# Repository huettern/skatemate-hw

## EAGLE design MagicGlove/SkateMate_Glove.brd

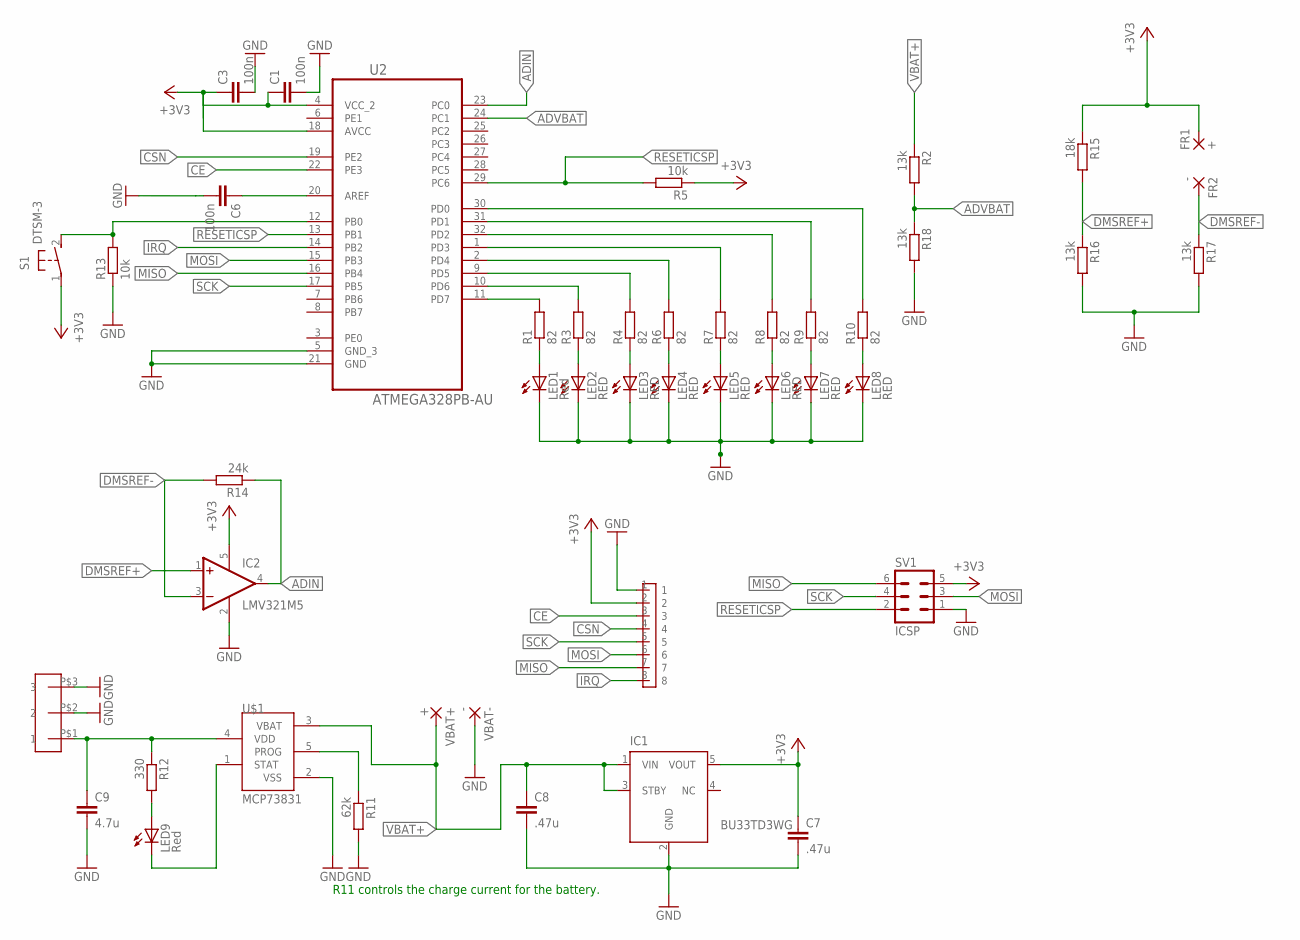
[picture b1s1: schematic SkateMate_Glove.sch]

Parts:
C1, C3, C6: 100n; C0603
C7, C8: .47u; C0603
C9: 4.7u; C0603
FR1: +; 1,6/0,8
FR2: -; 1,6/0,8
IC1: BU33TD3WG; SOT23-5
IC2: LMV321M5; SOT23-5
LED1, LED9: Red; CHIPLED_0805
LED2, LED3, LED4, LED5, LED6, LED7, LED8: RED; CHIPLED_0805
R1, R3, R4, R6, R7, R8, R9, R10: 82; R0603
R2, R16, R17, R18: 13k; R0603
R5, R13: 10k; R0603
R11: 62k; R0603
R12: 330; R0603
R14: 24k; R0603
R15: 18k; R0603
S1: DTSM-3
SV1: ICSP; MA03-2
U2: ATMEGA328PB-AU; QFP80P900X900X120-32N
U$1: MCP73831; SOT23-5L
U$2: HEADER1,27
U$3: 3PINHEADER
VBAT+: +; 1,6/0,8
VBAT-: -; 1,6/0,8

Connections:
+3V3: C1.1, C3.1, C7.1, FR1.1, IC1.5 (VOUT), IC2.5 (V+), R5.1, R15.1, S1.1, SV1.5, U2.4 (VCC_2), U2.18 (AVCC), U$2.2
ADIN: IC2.4 (OUT), R14.1, U2.23 (PC0)
ADVBAT: R2.2, R18.1, U2.24 (PC1)
CE: U2.22 (PE3), U$2.3
CSN: U2.19 (PE2), U$2.4
DMSREF+: IC2.1 (+IN), R15.2, R16.1
DMSREF-: FR2.1, IC2.3 (-IN), R14.2, R17.1
GND: C1.2, C3.2, C6.2, C7.2, C8.2, C9.2, IC1.2 (GND), IC2.2 (V-), LED1.C, LED2.C, LED3.C, LED4.C, LED5.C, LED6.C, LED7.C, LED8.C, R11.2, R13.1, R16.2, R17.2, R18.2, SV1.1, U2.5 (GND_3), U2.21 (GND), U$1.2 (VSS), U$2.1, U$3.P$2 (2), U$3.P$3 (3), VBAT-.1
IRQ: U2.14 (PB2), U$2.8
MISO: SV1.6, U2.16 (PB4), U$2.7
MOSI: SV1.3, U2.15 (PB3), U$2.6
unnamed: LED1.A, R1.1
unnamed: LED2.A, R3.1
unnamed: R13.2, S1.2, U2.12 (PB0)
unnamed: C6.1, U2.20 (AREF)
unnamed: R11.1, U$1.5 (PROG)
unnamed: LED3.A, R4.1
unnamed: LED6.A, R8.1
unnamed: LED7.A, R9.1
unnamed: LED8.A, R10.1
unnamed: LED4.A, R6.1
unnamed: LED5.A, R7.1
unnamed: R1.2, U2.11 (PD7)
unnamed: R3.2, U2.10 (PD6)
unnamed: R4.2, U2.9 (PD5)
unnamed: R6.2, U2.2 (PD4)
unnamed: R7.2, U2.1 (PD3)
unnamed: R8.2, U2.32 (PD2)
unnamed: R9.2, U2.31 (PD1)
unnamed: R10.2, U2.30 (PD0)
unnamed: LED9.A, R12.2
unnamed: LED9.C, U$1.1 (STAT)
unnamed: C9.1, R12.1, U$1.4 (VDD), U$3.P$1 (1)
RESETICSP: R5.2, SV1.2, U2.13 (PB1), U2.29 (PC6)
SCK: SV1.4, U2.17 (PB5), U$2.5
VBAT+: C8.1, IC1.1 (VIN), IC1.3 (STBY), R2.1, U$1.3 (VBAT), VBAT+.1

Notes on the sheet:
R11 controls the charge current for the battery.

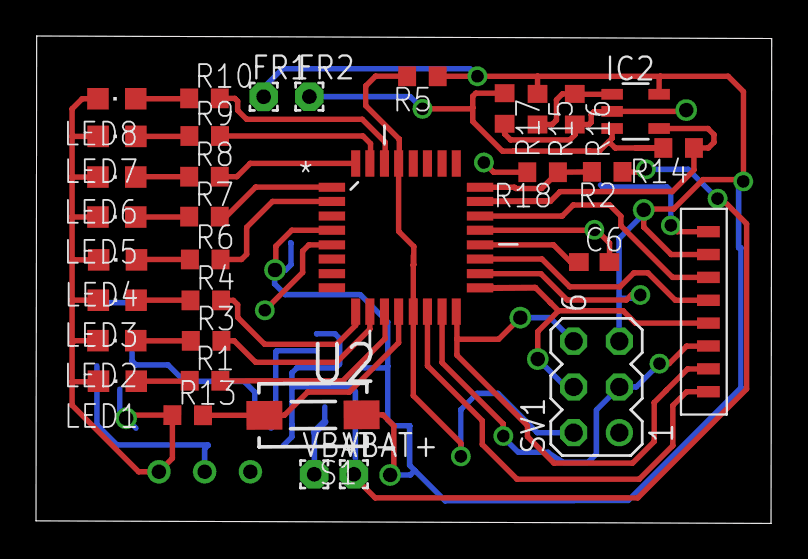
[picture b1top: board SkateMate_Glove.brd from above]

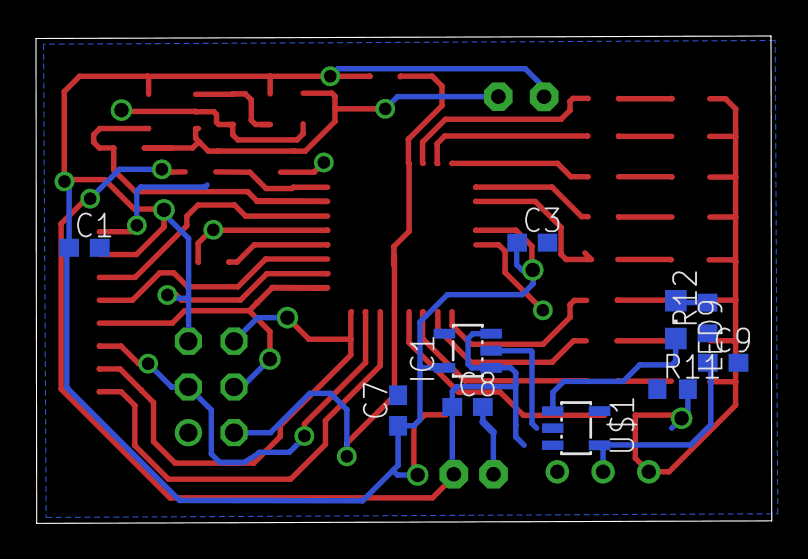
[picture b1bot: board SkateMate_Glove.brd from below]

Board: 2 copper layers, 40.9 x 27.1 mm, 45 parts (10 on the bottom side), 36 nets.

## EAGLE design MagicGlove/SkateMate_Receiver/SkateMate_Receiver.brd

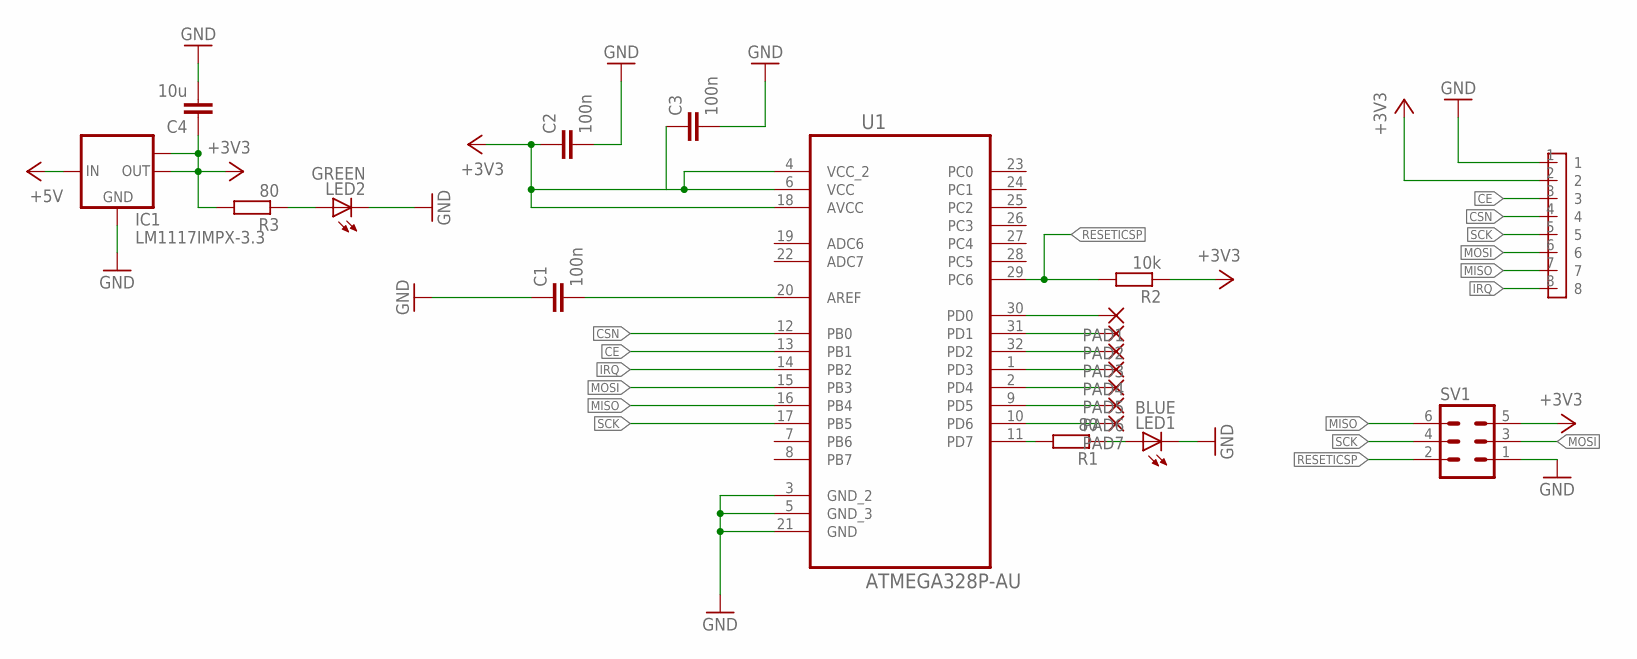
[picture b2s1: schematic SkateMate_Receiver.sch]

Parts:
C1, C2, C3: 100n; C0603
C4: 10u; C0603
IC1: LM1117IMPX-3.3; SOT223
LED1: BLUE; LED_SML0603
LED2: GREEN; LED_SML0603
PAD1, PAD2, PAD3, PAD4, PAD5, PAD6, PAD7: 1,6/0,8
R1, R3: 80; R0603
R2: 10k; R0603
SV1: MA03-2
U1: ATMEGA328P-AU; QFP80P900X900X120-32N
U$1: HEADER1,27

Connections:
+3V3: C2.1, C3.1, C4.1, IC1.2 (OUT), IC1.TAB (OUT1), R2.1, R3.2, SV1.5, U1.4 (VCC_2), U1.6 (VCC), U1.18 (AVCC), U$1.2
+5V: IC1.3 (IN)
CE: U1.13 (PB1), U$1.3
CSN: U1.12 (PB0), U$1.4
GND: C1.1, C2.2, C3.2, C4.2, IC1.1 (GND), LED1.C, LED2.C, SV1.1, U1.3 (GND_2), U1.5 (GND_3), U1.21 (GND), U$1.1
IRQ: U1.14 (PB2), U$1.8
MISO: SV1.6, U1.16 (PB4), U$1.7
MOSI: SV1.3, U1.15 (PB3), U$1.6
unnamed: R1.2, U1.11 (PD7)
unnamed: LED1.A, R1.1
unnamed: PAD1.1, U1.30 (PD0)
unnamed: PAD2.1, U1.31 (PD1)
unnamed: PAD3.1, U1.32 (PD2)
unnamed: PAD4.1, U1.1 (PD3)
unnamed: PAD5.1, U1.2 (PD4)
unnamed: C1.2, U1.20 (AREF)
unnamed: PAD6.1, U1.9 (PD5)
unnamed: PAD7.1, U1.10 (PD6)
unnamed: LED2.A, R3.1
RESETICSP: R2.2, SV1.2, U1.29 (PC6)
SCK: SV1.4, U1.17 (PB5), U$1.5

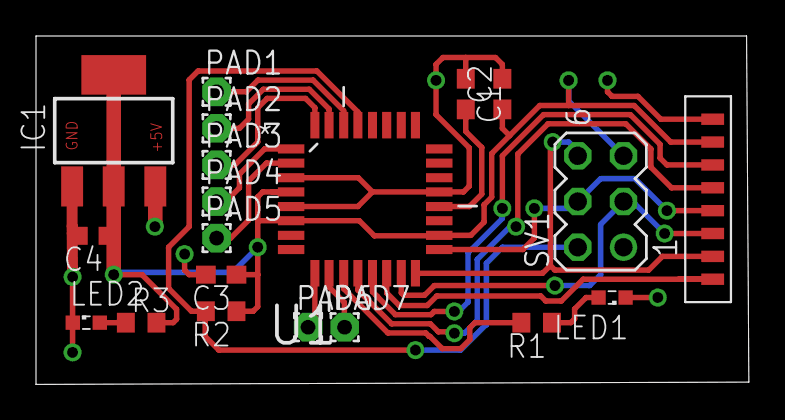
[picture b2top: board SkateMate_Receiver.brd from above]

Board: 2 copper layers, 39.6 x 19.4 mm, 20 parts (0 on the bottom side), 20 nets.

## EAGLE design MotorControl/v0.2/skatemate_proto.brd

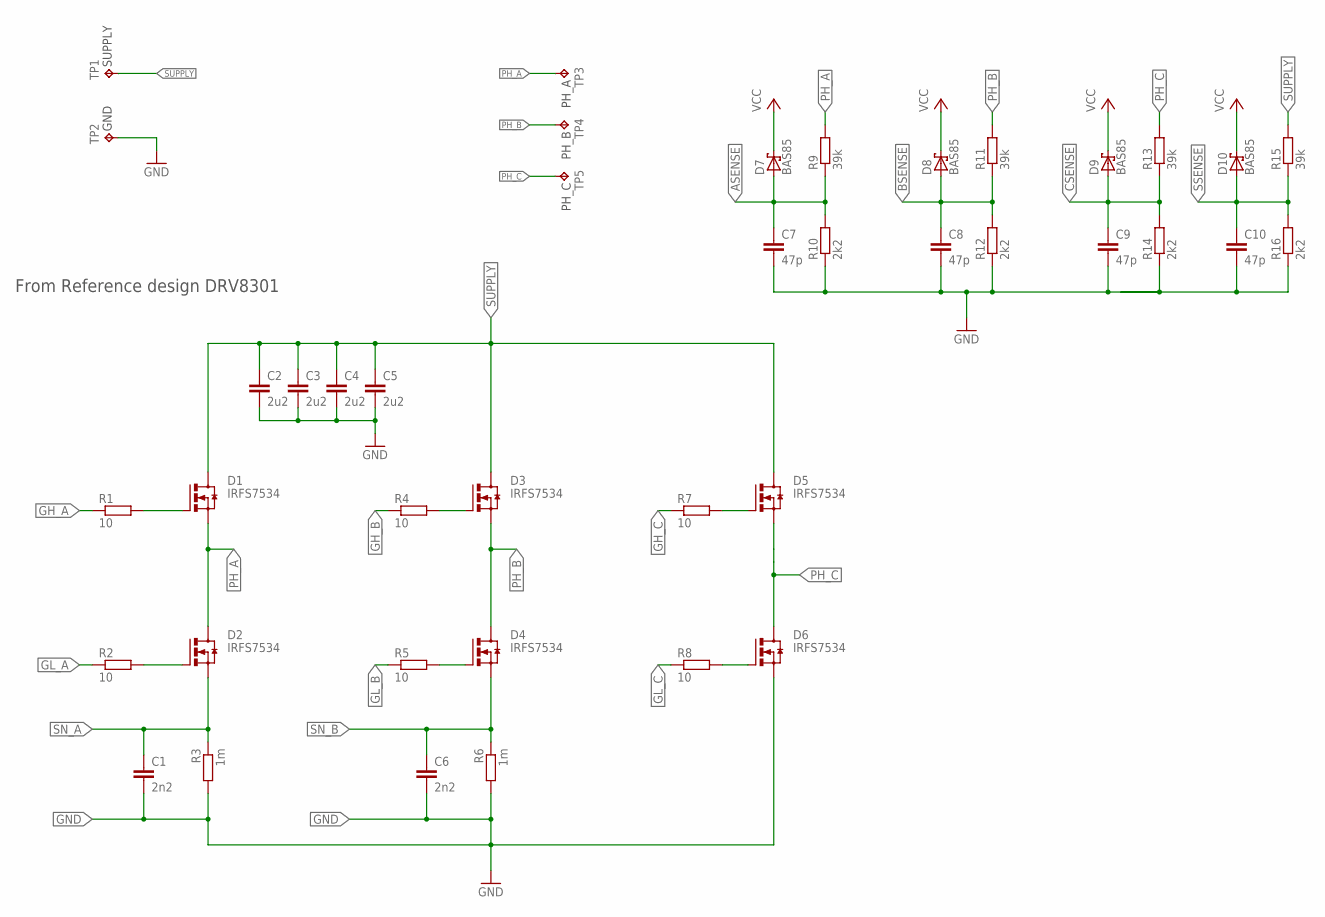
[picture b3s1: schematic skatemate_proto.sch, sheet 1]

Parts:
C1, C6: 2n2; C0805
C2, C3, C4, C5: 2u2; C1206
C7, C8, C9, C10: 47p; C0805
D1, D2, D3, D4, D5, D6: IRFS7534; D2PAK-7
D7, D8, D9, D10: BAS85; SOD80C
R1, R2, R4, R5, R7, R8: 10; R0805
R3, R6: 1m; R2512
R9, R11, R13, R15: 39k; R0805
R10, R12, R14, R16: 2k2; R0805
TP1: SUPPLY; SMD_M_1006
TP2: GND; SMD_M_1006
TP3: PH_A; SMD_M_1006
TP4: PH_B; SMD_M_1006
TP5: PH_C; SMD_M_1006

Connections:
ASENSE: C7.1, D7.A, R9.1, R10.2; also elsewhere on the board
BSENSE: C8.1, D8.A, R11.1, R12.2; also elsewhere on the board
CSENSE: C9.1, D9.A, R13.1, R14.2; also elsewhere on the board
GH_A: R1.1; also elsewhere on the board
GH_B: R4.1; also elsewhere on the board
GH_C: R7.1; also elsewhere on the board
GL_A: R2.1; also elsewhere on the board
GL_B: R5.1; also elsewhere on the board
GL_C: R8.1; also elsewhere on the board
GND: C1.2, C2.2, C3.2, C4.2, C5.2, C6.2, C7.2, C8.2, C9.2, C10.2, D6.S1 (S), D6.S2 (S), D6.S3 (S), D6.S4 (S), D6.S5 (S), R3.2, R6.2, R10.1, R12.1, R14.1, R16.1, TP2.P$1; also elsewhere on the board
unnamed: D1.G, R1.2
unnamed: D2.G, R2.2
unnamed: D4.G, R5.2
unnamed: D3.G, R4.2
unnamed: D5.G, R7.2
unnamed: D6.G, R8.2
PH_A: D1.S1 (S), D1.S2 (S), D1.S3 (S), D1.S4 (S), D1.S5 (S), D2.D, R9.2, TP3.P$1; also elsewhere on the board
PH_B: D3.S1 (S), D3.S2 (S), D3.S3 (S), D3.S4 (S), D3.S5 (S), D4.D, R11.2, TP4.P$1; also elsewhere on the board
PH_C: D5.S1 (S), D5.S2 (S), D5.S3 (S), D5.S4 (S), D5.S5 (S), D6.D, R13.2, TP5.P$1; also elsewhere on the board
SN_A: C1.1, D2.S1 (S), D2.S2 (S), D2.S3 (S), D2.S4 (S), D2.S5 (S), R3.1; also elsewhere on the board
SN_B: C6.1, D4.S1 (S), D4.S2 (S), D4.S3 (S), D4.S4 (S), D4.S5 (S), R6.1; also elsewhere on the board
SSENSE: C10.1, D10.A, R15.1, R16.2; also elsewhere on the board
SUPPLY: C2.1, C3.1, C4.1, C5.1, D1.D, D3.D, D5.D, R15.2, TP1.P$1; also elsewhere on the board
VCC: D7.C, D8.C, D9.C, D10.C; also elsewhere on the board

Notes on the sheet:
From Reference design DRV8301

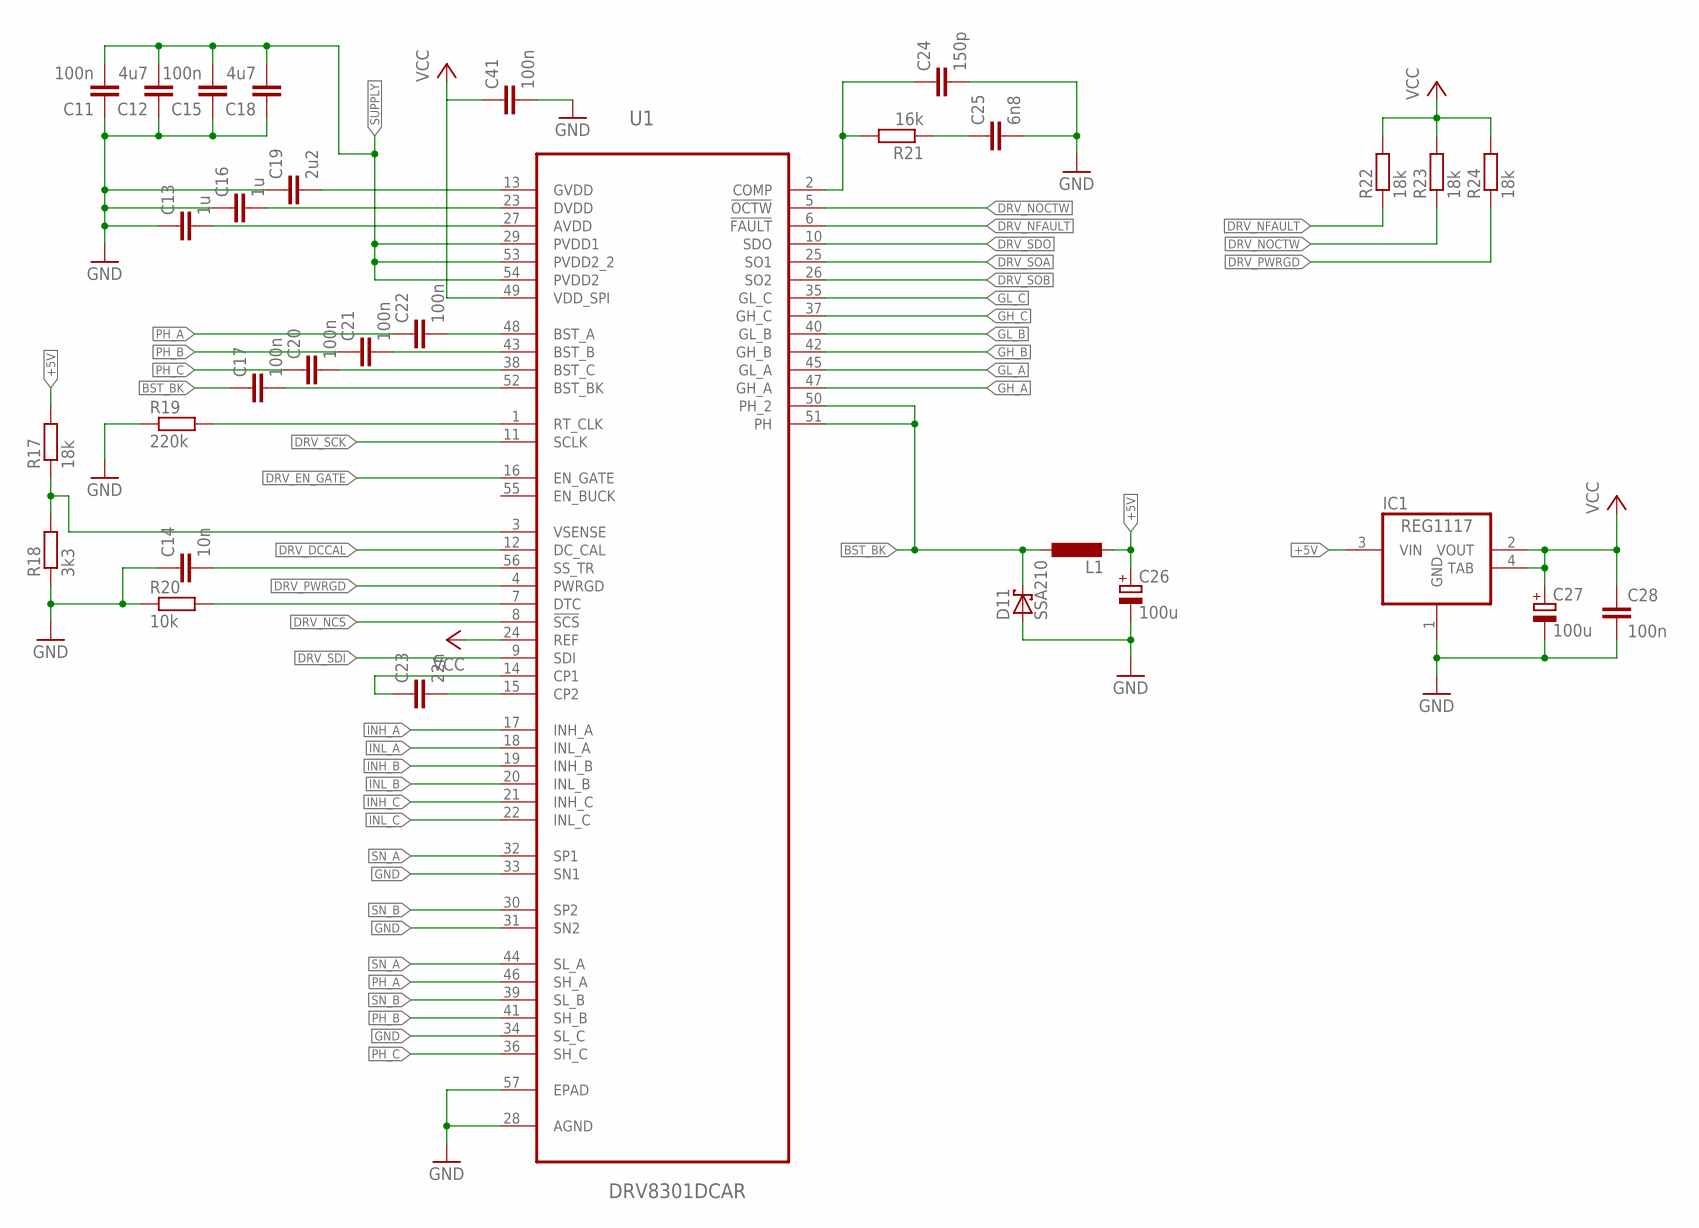
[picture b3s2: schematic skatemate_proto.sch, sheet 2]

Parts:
C11, C15, C17, C20, C21, C22, C28, C41: 100n; C0805
C12, C18: 4u7; C1206
C13, C16: 1u; C1206
C14: 10n; C0805
C19: 2u2; C1206
C23: 22n; C0805
C24: 150p; C0805
C25: 6n8; C0805
C26, C27: 100u; B/3528-21W
D11: SSA210; DO-214AA
IC1: REG1117; SOT223
L1: L-EUSDR0805; SDR0805
R17, R22, R23, R24: 18k; R0805
R18: 3k3; R0805
R19: 220k; R0805
R20: 10k; R0805
R21: 16k; R0805
U1: DRV8301DCAR; SOP50P810X120-57N

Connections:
+5V: C26.+, IC1.3 (VIN), L1.2, R17.2
BST_BK: C17.1, D11.C, L1.1, U1.50 (PH_2), U1.51 (PH)
DRV_DCCAL: U1.12 (DC_CAL); also elsewhere on the board
DRV_EN_GATE: U1.16 (EN_GATE); also elsewhere on the board
DRV_NCS: U1.8 (!SCS); also elsewhere on the board
DRV_NFAULT: R22.1, U1.6 (!FAULT); also elsewhere on the board
DRV_NOCTW: R23.1, U1.5 (!OCTW); also elsewhere on the board
DRV_PWRGD: R24.1, U1.4 (PWRGD); also elsewhere on the board
DRV_SCK: U1.11 (SCLK); also elsewhere on the board
DRV_SDI: U1.9 (SDI); also elsewhere on the board
DRV_SDO: U1.10 (SDO); also elsewhere on the board
DRV_SOA: U1.25 (SO1); also elsewhere on the board
DRV_SOB: U1.26 (SO2); also elsewhere on the board
GH_A: U1.47 (GH_A); also elsewhere on the board
GH_B: U1.42 (GH_B); also elsewhere on the board
GH_C: U1.37 (GH_C); also elsewhere on the board
GL_A: U1.45 (GL_A); also elsewhere on the board
GL_B: U1.40 (GL_B); also elsewhere on the board
GL_C: U1.35 (GL_C); also elsewhere on the board
GND: C11.1, C12.1, C13.1, C14.1, C15.1, C16.1, C18.1, C19.1, C24.2, C25.2, C26.-, C27.-, C28.2, C41.2, D11.A, IC1.1 (GND), R18.1, R19.1, R20.1, U1.28 (AGND), U1.31 (SN2), U1.33 (SN1), U1.34 (SL_C), U1.57 (EPAD); also elsewhere on the board
INH_A: U1.17 (INH_A); also elsewhere on the board
INH_B: U1.19 (INH_B); also elsewhere on the board
INH_C: U1.21 (INH_C); also elsewhere on the board
INL_A: U1.18 (INL_A); also elsewhere on the board
INL_B: U1.20 (INL_B); also elsewhere on the board
INL_C: U1.22 (INL_C); also elsewhere on the board
unnamed: C23.2, U1.15 (CP2)
unnamed: C23.1, U1.14 (CP1)
unnamed: R20.2, U1.7 (DTC)
unnamed: R17.1, R18.2, U1.3 (VSENSE)
unnamed: C14.2, U1.56 (SS_TR)
unnamed: R19.2, U1.1 (RT_CLK)
unnamed: C22.2, U1.48 (BST_A)
unnamed: C21.2, U1.43 (BST_B)
unnamed: C20.2, U1.38 (BST_C)
unnamed: C17.2, U1.52 (BST_BK)
unnamed: C19.2, U1.13 (GVDD)
unnamed: C16.2, U1.23 (DVDD)
unnamed: C13.2, U1.27 (AVDD)
unnamed: C24.1, R21.2, U1.2 (COMP)
unnamed: C25.1, R21.1
PH_A: C22.1, U1.46 (SH_A); also elsewhere on the board
PH_B: C21.1, U1.41 (SH_B); also elsewhere on the board
PH_C: C20.1, U1.36 (SH_C); also elsewhere on the board
SN_A: U1.32 (SP1), U1.44 (SL_A); also elsewhere on the board
SN_B: U1.30 (SP2), U1.39 (SL_B); also elsewhere on the board
SUPPLY: C11.2, C12.2, C15.2, C18.2, U1.29 (PVDD1), U1.53 (PVDD2_2), U1.54 (PVDD2); also elsewhere on the board
VCC: C27.+, C28.1, C41.1, IC1.2 (VOUT), IC1.4 (TAB), R22.2, R23.2, R24.2, U1.24 (REF), U1.49 (VDD_SPI); also elsewhere on the board

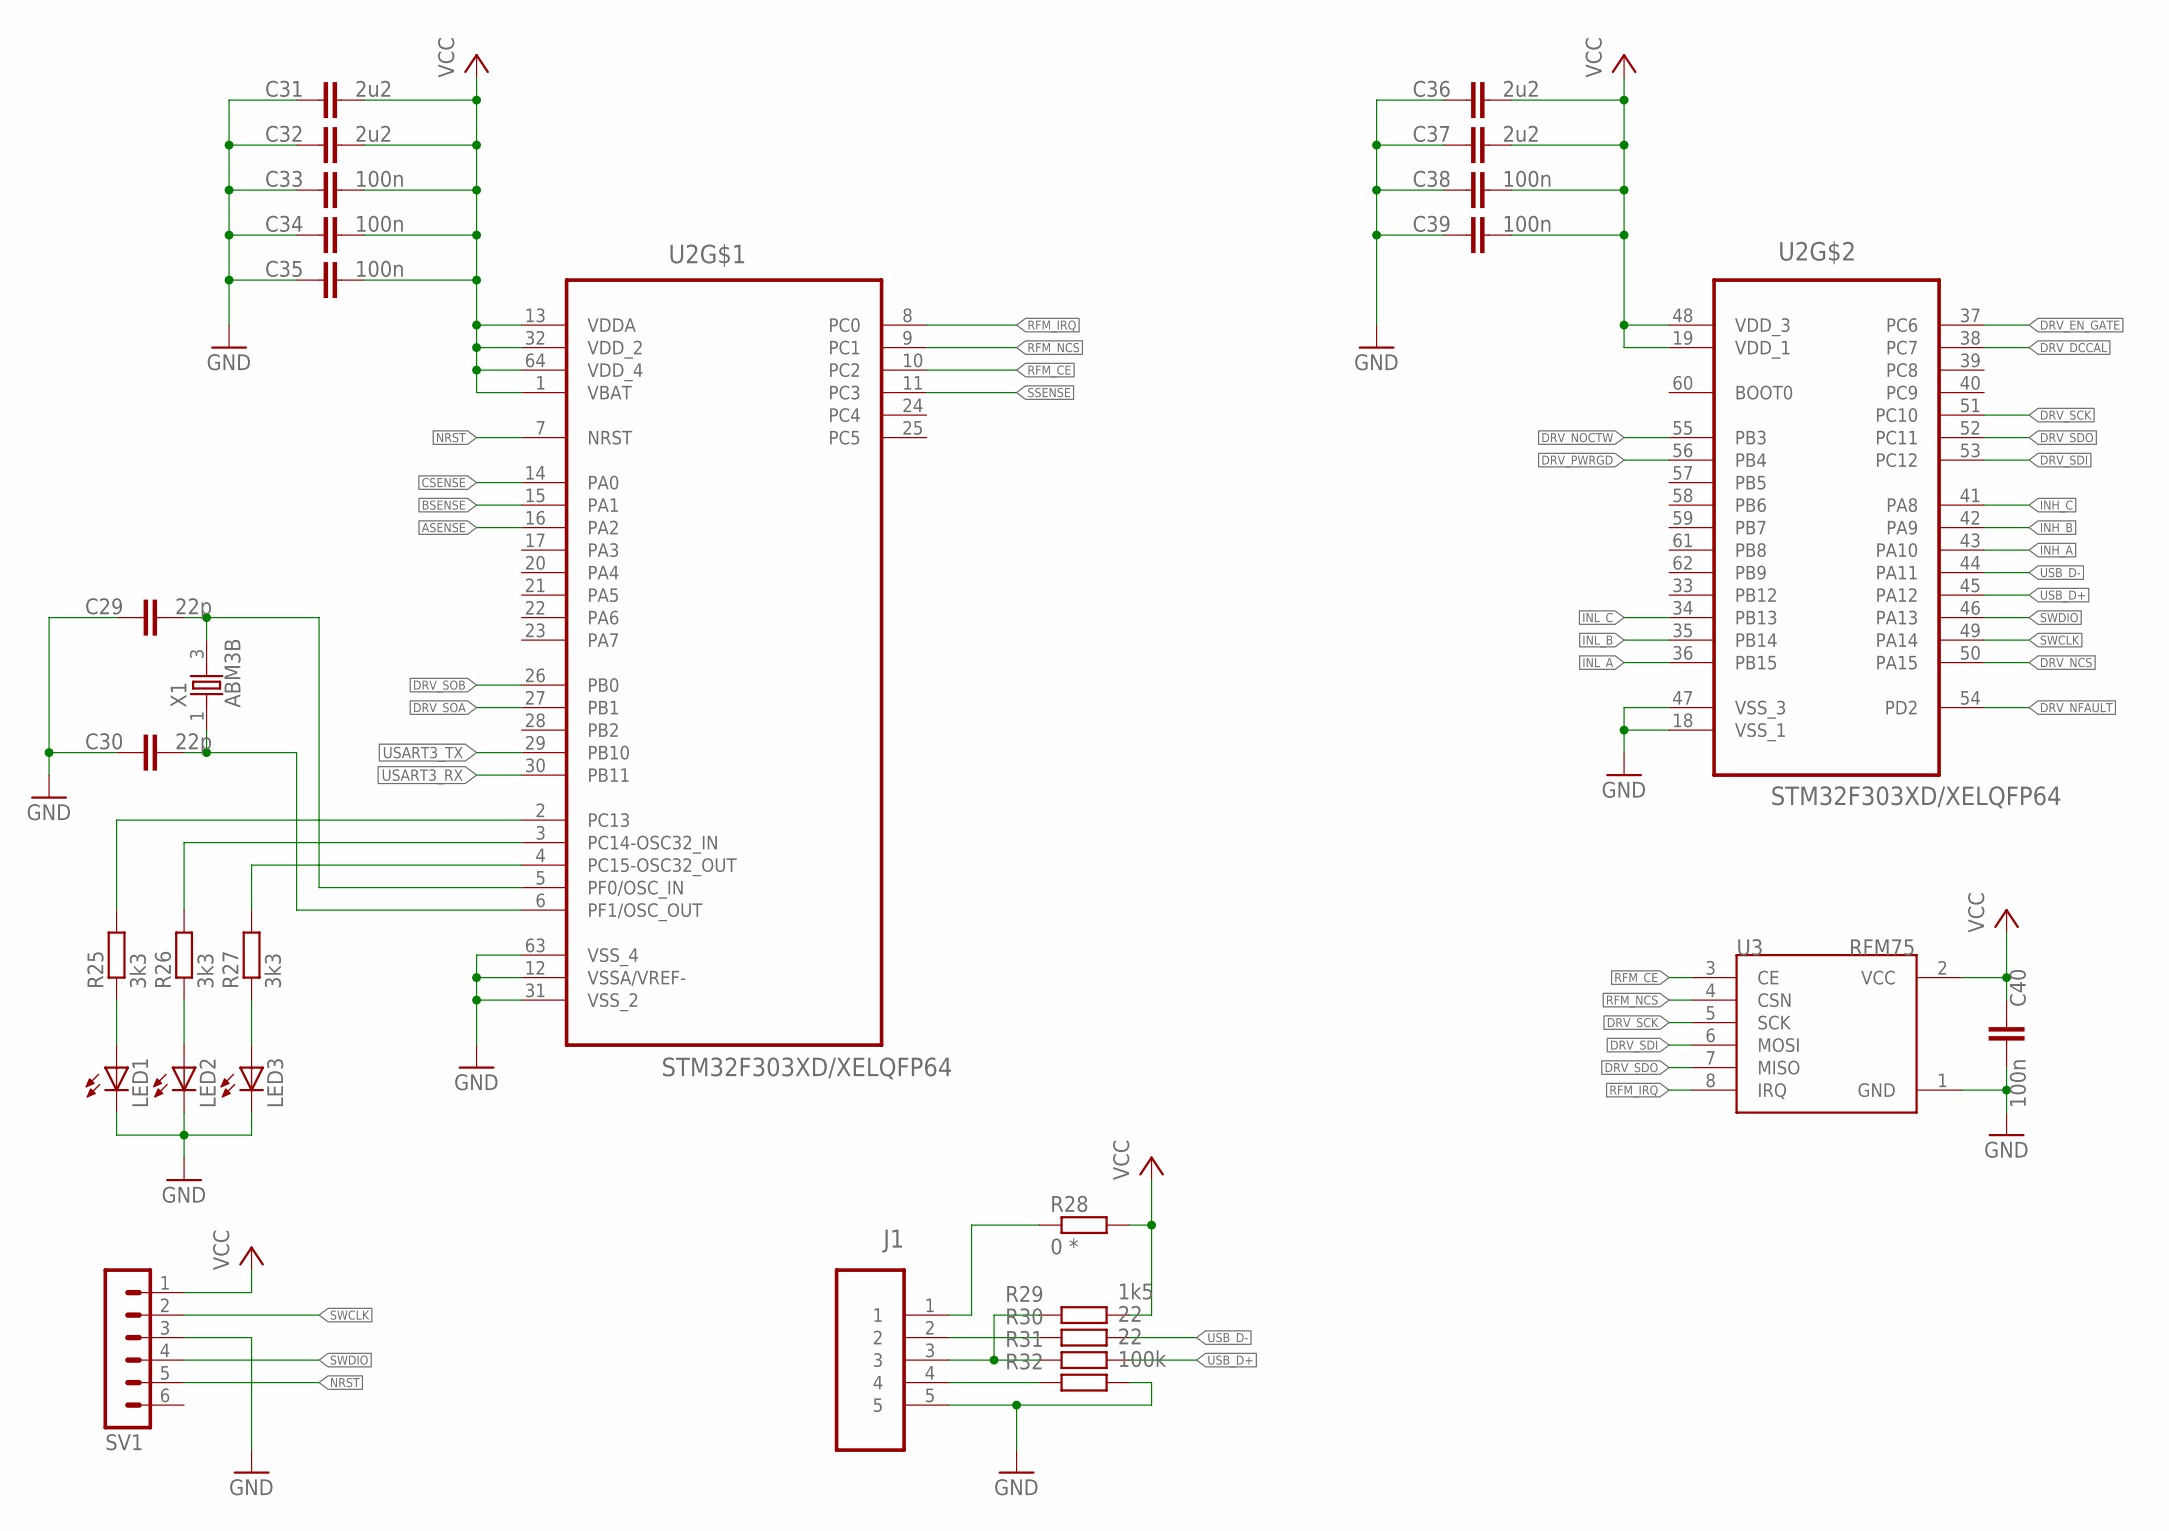
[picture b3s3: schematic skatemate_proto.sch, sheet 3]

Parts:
C29, C30: 22p; C0805
C31, C32, C36, C37: 2u2; C0805
C33, C34, C35, C38, C39, C40: 100n; C0805
J1: 47346-0001; MOLEX_47346-0001
LED1, LED2, LED3: LEDCHIP-LED0805; CHIP-LED0805
R25, R26, R27: 3k3; R0805
R28: 0 *; R0805
R29: 1k5; R0805
R30, R31: 22; R0805
R32: 100k; R0805
SV1: MA06-1
U2: STM32F303XD/XELQFP64; LQFP64
U3: RFM75
X1: ABM3B; IQG5032B

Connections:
ASENSE: U2.16 (PA2); also elsewhere on the board
BSENSE: U2.15 (PA1); also elsewhere on the board
CSENSE: U2.14 (PA0); also elsewhere on the board
DRV_DCCAL: U2.38 (PC7); also elsewhere on the board
DRV_EN_GATE: U2.37 (PC6); also elsewhere on the board
DRV_NCS: U2.50 (PA15); also elsewhere on the board
DRV_NFAULT: U2.54 (PD2); also elsewhere on the board
DRV_NOCTW: U2.55 (PB3); also elsewhere on the board
DRV_PWRGD: U2.56 (PB4); also elsewhere on the board
DRV_SCK: U2.51 (PC10), U3.5 (SCK); also elsewhere on the board
DRV_SDI: U2.53 (PC12), U3.6 (MOSI); also elsewhere on the board
DRV_SDO: U2.52 (PC11), U3.7 (MISO); also elsewhere on the board
DRV_SOA: U2.27 (PB1); also elsewhere on the board
DRV_SOB: U2.26 (PB0); also elsewhere on the board
GND: C29.1, C30.1, C31.1, C32.1, C33.1, C34.1, C35.1, C36.1, C37.1, C38.1, C39.1, C40.2, J1.5, LED1.C, LED2.C, LED3.C, R32.2, SV1.3, U2.12 (VSSA/VREF-), U2.18 (VSS_1), U2.31 (VSS_2), U2.47 (VSS_3), U2.63 (VSS_4), U3.1 (GND); also elsewhere on the board
INH_A: U2.43 (PA10); also elsewhere on the board
INH_B: U2.42 (PA9); also elsewhere on the board
INH_C: U2.41 (PA8); also elsewhere on the board
INL_A: U2.36 (PB15); also elsewhere on the board
INL_B: U2.35 (PB14); also elsewhere on the board
INL_C: U2.34 (PB13); also elsewhere on the board
unnamed: J1.4, R32.1
unnamed: J1.3, R29.1, R31.1
unnamed: J1.2, R30.1
unnamed: J1.1, R28.1
unnamed: R27.2, U2.4 (PC15-OSC32_OUT)
unnamed: R26.2, U2.3 (PC14-OSC32_IN)
unnamed: R25.2, U2.2 (PC13)
unnamed: LED1.A, R25.1
unnamed: LED2.A, R26.1
unnamed: LED3.A, R27.1
unnamed: C30.2, U2.6 (PF1/OSC_OUT), X1.1
unnamed: C29.2, U2.5 (PF0/OSC_IN), X1.3 (2)
NRST: SV1.5, U2.7 (NRST)
RFM_CE: U2.10 (PC2), U3.3 (CE)
RFM_IRQ: U2.8 (PC0), U3.8 (IRQ)
RFM_NCS: U2.9 (PC1), U3.4 (CSN)
SSENSE: U2.11 (PC3); also elsewhere on the board
SWCLK: SV1.2, U2.49 (PA14)
SWDIO: SV1.4, U2.46 (PA13)
USART3_RX: U2.30 (PB11)
USART3_TX: U2.29 (PB10)
USB_D+: R31.2, U2.45 (PA12)
USB_D-: R30.2, U2.44 (PA11)
VCC: C31.2, C32.2, C33.2, C34.2, C35.2, C36.2, C37.2, C38.2, C39.2, C40.1, R28.2, R29.2, SV1.1, U2.1 (VBAT), U2.13 (VDDA), U2.19 (VDD_1), U2.32 (VDD_2), U2.48 (VDD_3), U2.64 (VDD_4), U3.2 (VCC); also elsewhere on the board

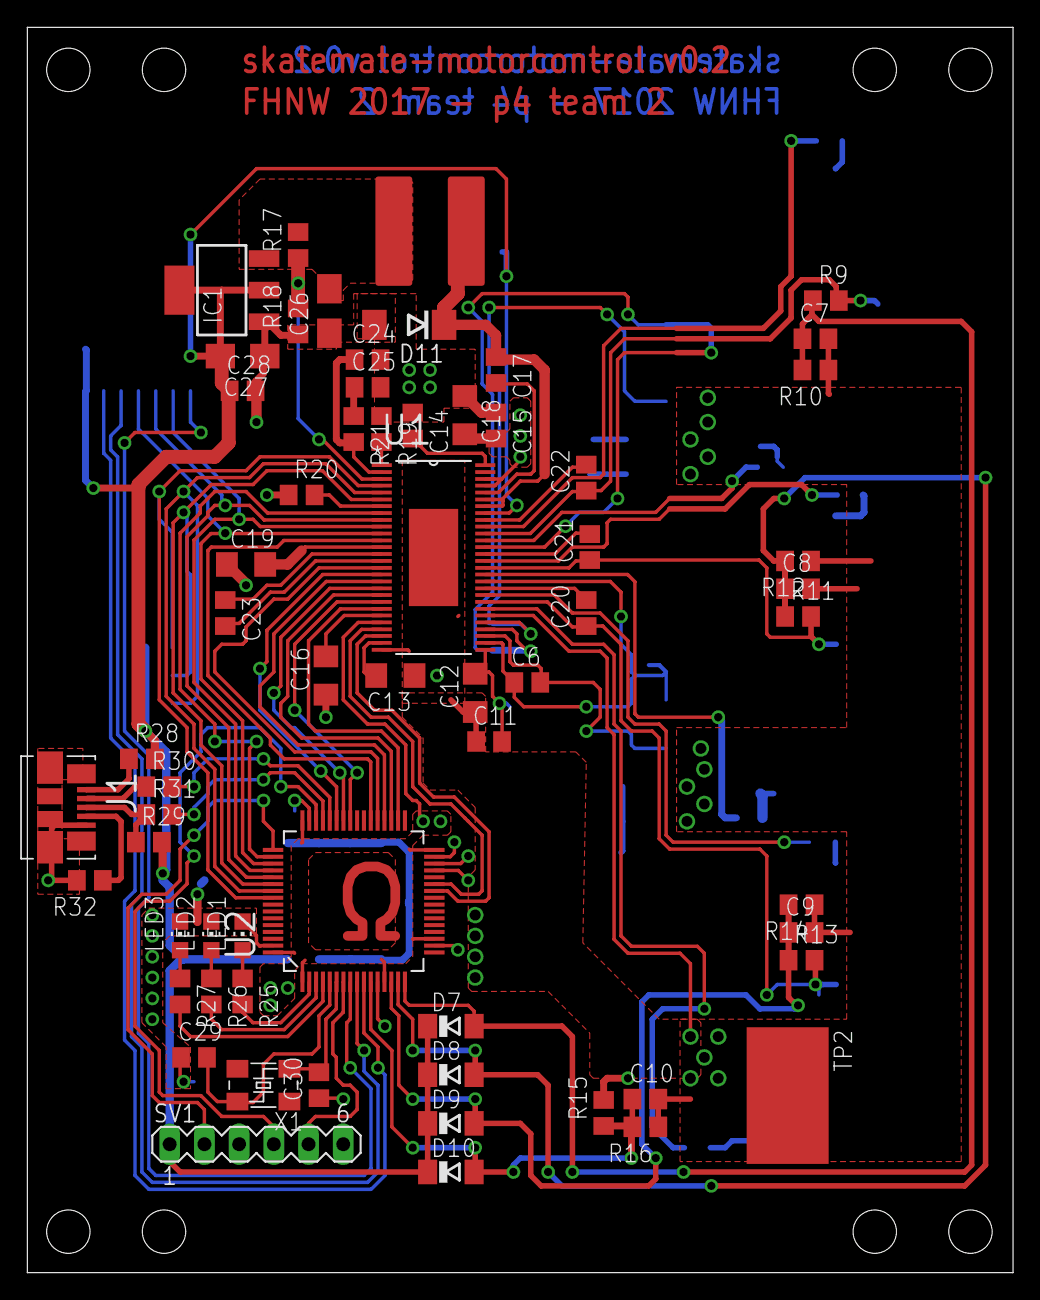
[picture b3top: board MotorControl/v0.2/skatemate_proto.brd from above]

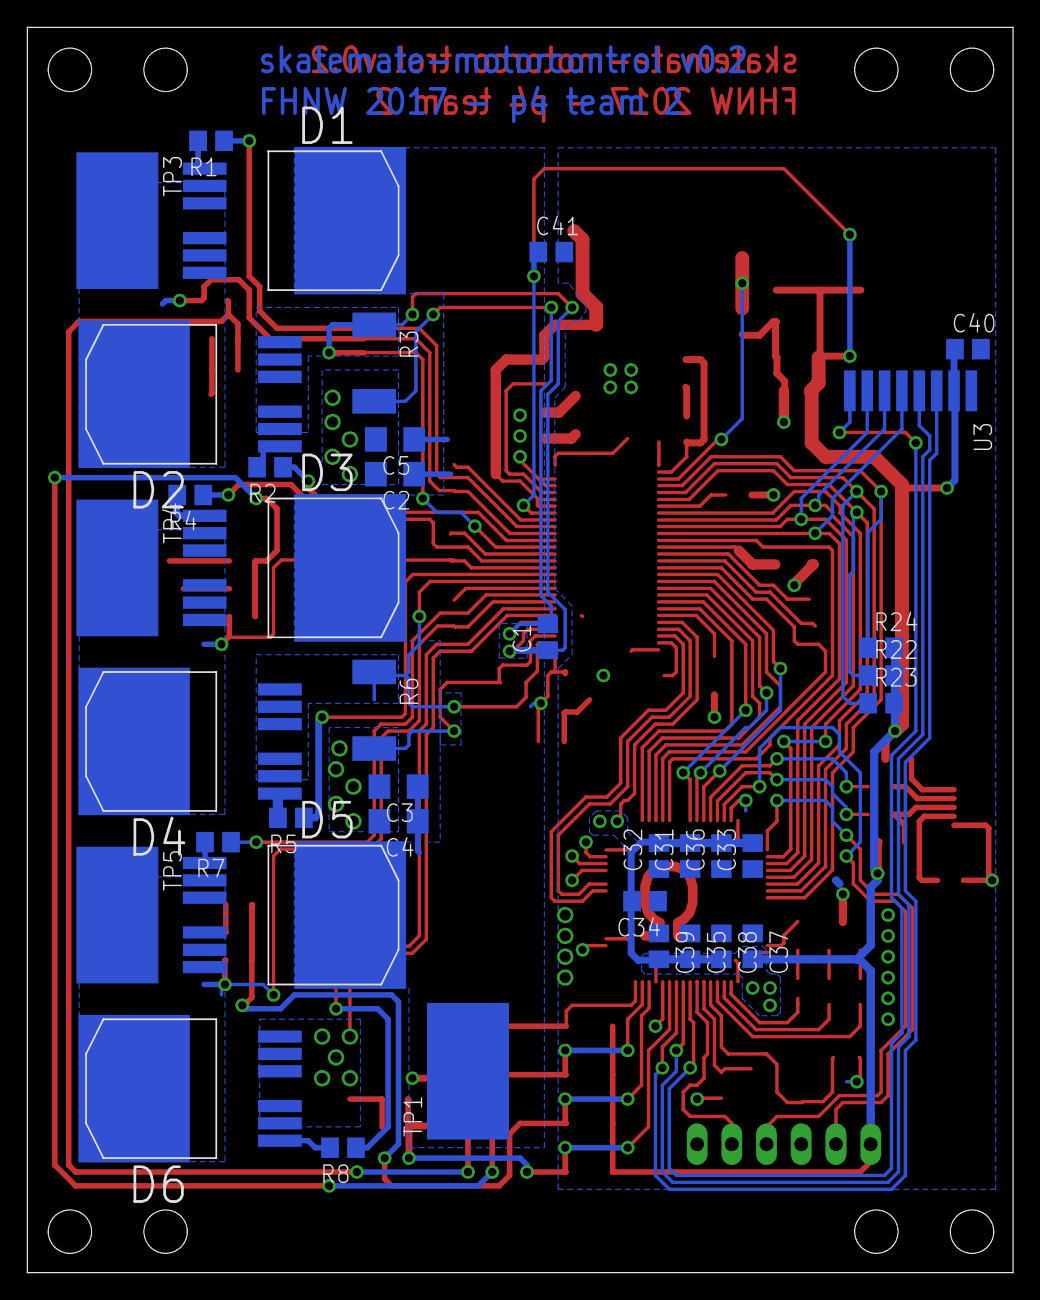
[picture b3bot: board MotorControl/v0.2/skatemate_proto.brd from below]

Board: 2 copper layers, 72.1 x 91.1 mm, 100 parts (38 on the bottom side), 78 nets.

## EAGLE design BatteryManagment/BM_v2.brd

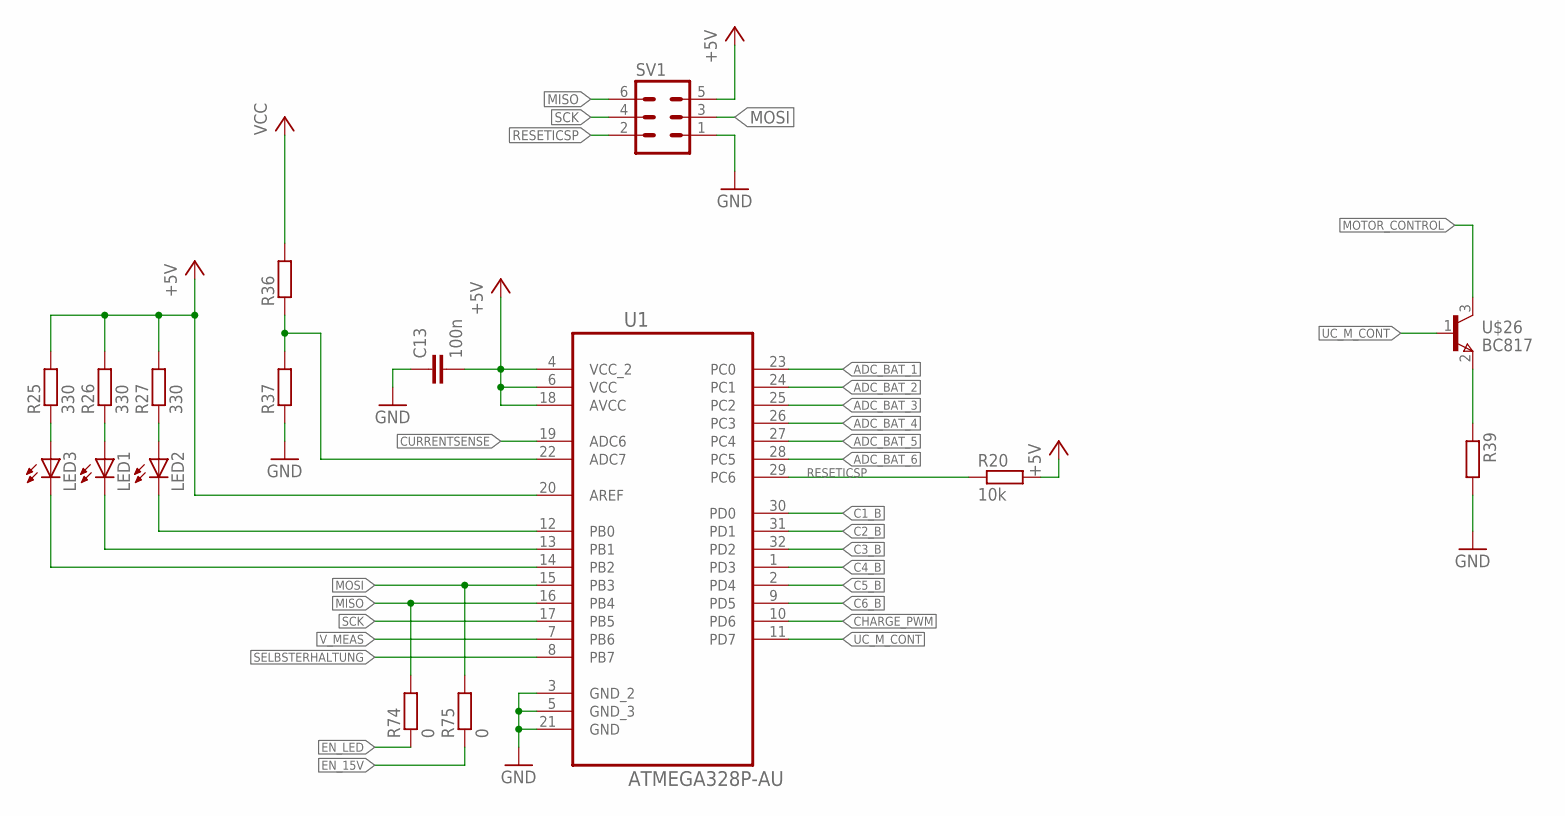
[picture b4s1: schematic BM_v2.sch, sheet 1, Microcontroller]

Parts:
C13: 100n; C0603
LED1, LED2, LED3: LED_E; LED_1206
R20: 10k; R0603
R25, R26, R27: 330; R0603
R36, R37, R39: R-EU_R0603; R0603
R74, R75: 0; R0603
SV1: MA03-2
U1: ATMEGA328P-AU; QFP80P900X900X120-32N
U$26: BC817; SOT23

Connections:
+5V: C13.2, R20.2, R25.2, R26.2, R27.2, SV1.5, U1.4 (VCC_2), U1.6 (VCC), U1.18 (AVCC), U1.20 (AREF); also elsewhere on the board
ADC_BAT_1: U1.23 (PC0); also elsewhere on the board
ADC_BAT_2: U1.24 (PC1); also elsewhere on the board
ADC_BAT_3: U1.25 (PC2); also elsewhere on the board
ADC_BAT_4: U1.26 (PC3); also elsewhere on the board
ADC_BAT_5: U1.27 (PC4); also elsewhere on the board
ADC_BAT_6: U1.28 (PC5); also elsewhere on the board
C1_B: U1.30 (PD0); also elsewhere on the board
C2_B: U1.31 (PD1); also elsewhere on the board
C3_B: U1.32 (PD2); also elsewhere on the board
C4_B: U1.1 (PD3); also elsewhere on the board
C5_B: U1.2 (PD4); also elsewhere on the board
C6_B: U1.9 (PD5); also elsewhere on the board
CHARGE_PWM: U1.10 (PD6); also elsewhere on the board
CURRENTSENSE: U1.19 (ADC6); also elsewhere on the board
EN_15V: R75.1; also elsewhere on the board
EN_LED: R74.1; also elsewhere on the board
GND: C13.1, R37.1, R39.2, SV1.1, U1.3 (GND_2), U1.5 (GND_3), U1.21 (GND); also elsewhere on the board
MISO: R74.2, SV1.6, U1.16 (PB4)
MOSI: R75.2, SV1.3, U1.15 (PB3)
MOTOR_CONTROL: U$26.3 (C); also elsewhere on the board
unnamed: LED2.C, U1.12 (PB0)
unnamed: LED1.C, U1.13 (PB1)
unnamed: LED3.C, U1.14 (PB2)
unnamed: LED2.A, R27.1
unnamed: LED1.A, R26.1
unnamed: LED3.A, R25.1
unnamed: R39.1, U$26.2 (E)
unnamed: R36.1, R37.2, U1.22 (ADC7)
RESETICSP: R20.1, SV1.2, U1.29 (PC6)
SCK: SV1.4, U1.17 (PB5)
SELBSTERHALTUNG: U1.8 (PB7); also elsewhere on the board
UC_M_CONT: U1.11 (PD7), U$26.1 (B)
VCC: R36.2; also elsewhere on the board
V_MEAS: U1.7 (PB6); also elsewhere on the board
